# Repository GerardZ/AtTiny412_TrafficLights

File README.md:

# **AtTiny412 TrafficLight**

### **So, what is this ?**

Recently I bought a bunch of the new AtTiny412 series microcontroller, these controller have 8 pins, where 5 pins are useable by the user. They are programmed with the UPDI programming interface, occupying only one pin.

For a getting-to-know I quickly created this little project. It is a double trafficlight intended for a plain crossing.

The circuit is as simple as can be, 6 leds, 3 resistors, 1 capacitor, 1 attiny.

Techniques:

- Led multiplexing
- AtTiny412

Programmer:

I use a USB-C CH340 board, it is fitted with a 1k resistor seated between Rx and Tx, Rx is UPDI interface. IMPORANT: To get the thing going, I had to remove the leds fom the board. On hindsight, the Rx led would probably be sufficient but I removed all three of them (or there resistors)

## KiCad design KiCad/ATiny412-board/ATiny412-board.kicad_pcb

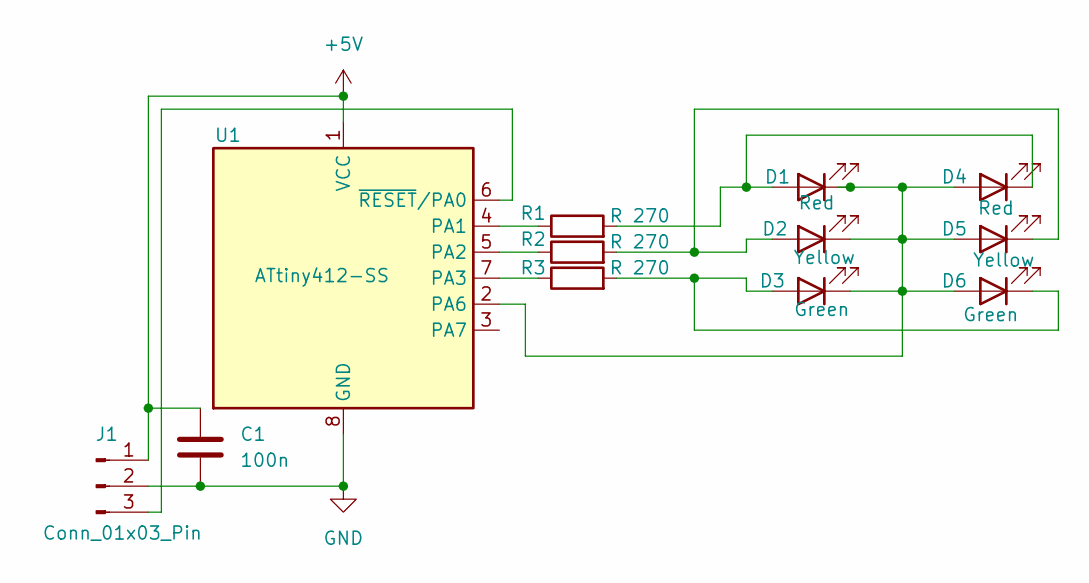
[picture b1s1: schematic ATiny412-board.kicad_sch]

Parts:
C1: 100n; C_1210_3225Metric_Pad1.33x2.70mm_HandSolder
D1, D4: Red; LED_D5.0mm
D2, D5: Yellow; LED_D5.0mm
D3, D6: Green; LED_D5.0mm
J1: Conn_01x03_Pin; PinHeader_1x03_P2.54mm_Vertical
R1, R2, R3: R 270; R_1206_3216Metric_Pad1.30x1.75mm_HandSolder
U1: ATtiny412-SS; SOIC-8_3.9x4.9mm_P1.27mm

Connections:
+5V: C1.1, J1.1, U1.1 (VCC)
GND: C1.2, J1.2, U1.8 (GND)
unnamed: D1.2 (A), D4.1 (K), R1.2
unnamed: D1.1 (K), D2.1 (K), D3.1 (K), D4.2 (A), D5.2 (A), D6.2 (A), U1.2 (PA6)
unnamed: D2.2 (A), D5.1 (K), R2.2
unnamed: D3.2 (A), D6.1 (K), R3.2
unnamed: J1.3, U1.6 (~RESET/PA0)
unnamed: R1.1, U1.4 (PA1)
unnamed: R2.1, U1.5 (PA2)
unnamed: R3.1, U1.7 (PA3)

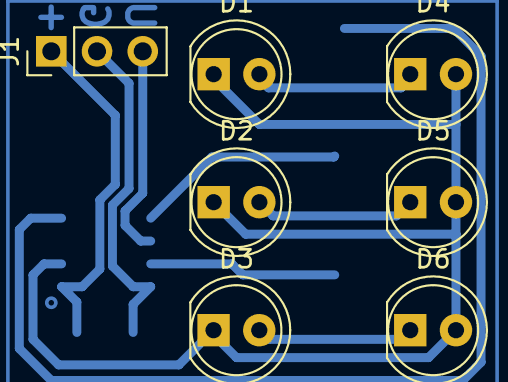
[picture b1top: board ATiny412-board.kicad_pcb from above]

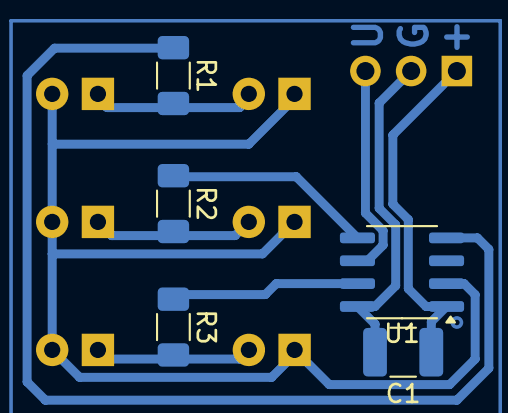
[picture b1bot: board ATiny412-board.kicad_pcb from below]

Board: 2 copper layers, 12 parts (5 on the bottom side), 10 nets.

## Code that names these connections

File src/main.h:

#include <Arduino.h>
#include <avr/io.h>
#include <avr/interrupt.h>

#define RED     PIN_PA1
#define YELLOW  PIN_PA2
#define GREEN   PIN_PA3
#define MUX     PIN_PA6

struct TrafficLights
{
  bool r1;
  bool y1;
  bool g1;
  bool r2;
  bool y2;
  bool g2;
  bool mux;
};

enum Action : uint8_t
{
  RED1_on,    // RED column 1 on
  RED1_off,   // RED column 1 off
  RED2_on,    // ... etc.
  RED2_off,
  YEL1_on,    
  YEL1_off,
  YEL2_on,
  YEL2_off,
  GRN1_on,
  GRN1_off,
  GRN2_on,
  GRN2_off,
  cRED1_on,   // clear all in column 1 & RED column 1 on
  cRED2_on,   // ... etc.
  cYEL1_on,
  cYEL2_on,
  cGRN1_on,
  cGRN2_on,
  ccYEL1_on,  // Turn on YEL1, turn off ALL others
  ccYEL2_on,
  PAUSE0,     // pause 0
  PAUSE1,
  PAUSE2,
  PAUSE3,
  ClrAll      // clear all
};

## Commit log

2024-04-25 Init
2024-04-29 picture
2024-05-05 USB-C UPDI
2024-07-27 updateje
2025-05-16 checking
